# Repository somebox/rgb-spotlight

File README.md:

# RGB Spotlight

Status (2026-11-03): v2 schematics and both boards done (DRC clean), with a failure review whose changes are planned but not yet applied. Start with [HANDOVER.md](HANDOVER.md).

Chainable, addressable 3 x 3 W RGB spotlight for 12 V installations: an aluminium LED board and an FR4 driver board in an aluminium cylinder.

- **v1** (EasyEDA, one FR4 board) was built but never lit: the PT4115 stages were wired as the wrong kind of buck, and the 74HC04 was unpowered.
- **v2** is a KiCad restart with two boards.

| Document | What's in it |
| --- | --- |
| [HANDOVER.md](HANDOVER.md) | how we got here, decisions, the work remaining |
| [DESIGN.md](DESIGN.md) | requirements, the v1 post-mortem, numbered decisions, circuit, thermal estimate, simulation (§2.7), open items |
| [LAYOUT.md](LAYOUT.md) | both PCBs: floor plans, rules, scripted copper and routing, outline presets, checks |
| [PRODUCTION.md](PRODUCTION.md) | order files, order checklist (polarity!), harness and bring-up, costs |
| [docs/reviews/](docs/reviews/) | pre-order failure review: findings, bench list, firmware duties |

## What it does

A high-power, addressable RGB pixel for spotlights and creative lighting. It speaks the WS2811 protocol, so it daisy-chains and works with FastLED, WLED and other WS2811-compatible software.

- **LED board** (aluminium, 1 layer, 50 mm):
  - three XINGLIGHT HD2525 3 W LEDs (R/G/B), spread on a 12 mm-radius ring;
  - each LED on its own heat-spreading copper island;
  - six wire pads around a centre hole for the harness.
- **Driver board** (FR4, 2 layers, 50 mm), mounted 4–6 cm behind the LED board:
  - WS2811 pixel controller;
  - three PT4115 constant-current bucks (455 mA each);
  - level shifter on DIN; inverter for the PWM polarity;
  - 78L05 logic rail; TVS on the 12 V input.

## Electrical specs

- **Supply:** 12 V (the PT4115 regulates down to about 6 V at the end of a chain)
- **Data:** WS2811 protocol, 800 kHz, single wire; 3.3 V or 5 V at DIN
- **LED current:** about 455 mA per channel (`I = 0.1 V / 0.22 Ω`); LEDs rated 1 A / 3 W
- **Full white:** 5.0 W, 0.42 A at 12 V per light (simulated, DESIGN.md §2.7); drivers about 80 % efficient
- **Chaining:** JST XH connectors (3 A) pass 12 V/GND through: up to 5 lights per fused 12 V feed, 2.2–2.6 A (DESIGN.md §2.4). Use a 36 W supply for 4 lights and 60 W for 5, and add a feed per group after that.
- **Heat:** about 2.7 W in the LED board, which needs a heatsink: the housing's heat plate. About 0.9 W in the driver, mostly in the three Schottky diodes. See DESIGN.md §2.6–2.7.
- **Dimming:** brightness follows the 8-bit level within 5 % above 20 % and within 20 % down to 5 %. The lowest few levels are unreliable (DESIGN.md §2.7).

## Connections

| Connector | Where | Pins |
| --- | --- | --- |
| J1 IN | driver, back (JST XH 3, vertical) | 1 `12V`, 2 `DATA`, 3 `GND` |
| J2 OUT | driver, back (JST XH 3, vertical) | 1 `12V`, 2 `DATA`, 3 `GND` |
| J3 LED | driver, front (JST PH 6, vertical) | 1 `R+`, 2 `R-`, 3 `G+`, 4 `G-`, 5 `B+`, 6 `B-` |
| TP1–TP6 | LED board, around the centre hole | same order as J3; solder the wires here |

J1 and J2 share one pin order, so chain with pin-1-to-pin-1 cables. v1 had J2 mirrored.

1. Connect the controller's data to J1 pin 2 of the first light, and +12 V / GND to pins 1 / 3. Keep controller and power grounds common.
2. Chain J2 of one light to J1 of the next.
3. Twist each colour's LED pair in the harness.

## Project layout

- `boards/led/`, `boards/driver/`: KiCad 10 projects. Schematics come from `scripts/sch_led.py` / `scripts/sch_driver.py`; boards from `scripts/make_led_pcb.sh` / `scripts/make_driver_pcb.sh`.
- `lib/`: project symbols, footprints and 3D models (`scripts/make_lib.py`).
- `scripts/`: generators and checks (`netcheck.py`, `ratsnest.py`, `make_previews.sh`, `make_fab.sh`); `pcbkit.toml` sets up pcb-kit's release and production record. The shared parts (schematic builder, silkscreen placer, DRC/ERC/board checks, previews, JLC fab files, ngspice runner) come from [pcb-kit](https://github.com/somebox/pcb-kit): `uv tool install -e ~/src/pcb-kit && pcbkit link`.
- `sim/`: ngspice simulation of one LED channel (`sim/channel.py`); tables and plots in `sim/results/`.
- `docs/previews/<board>/`: schematic PDF, board PNGs, 3D renders. `docs/previews/outline-presets.png` compares the board outline options.
- **Board outline:** everything sits in a 50 mm core. The edge is a preset, `disc50` (current), `disc55`, `disc60` or `tabs3` (screw tabs). Change it with `scripts/set_outline.py`; see LAYOUT.md.
- `archive/v1-easyeda/`: the v1 EasyEDA exports, a KiCad import of the v1 board, its as-built netlist and the bodge guide.

```bash
python3 scripts/sch_driver.py && python3 scripts/sch_led.py
pcbkit erc boards/driver/driver.kicad_sch && python3 scripts/netcheck.py
scripts/make_led_pcb.sh && scripts/make_driver_pcb.sh --force --route
pcbkit drc boards/driver/driver.kicad_pcb --save && pcbkit check boards/driver/driver.kicad_pcb
scripts/make_previews.sh all
pcbkit release --dry-run                                    # then pcbkit release: versioned order files in releases/ (PRODUCTION.md)
python3 sim/channel.py                                      # LED channel simulation
```

## BOM

- Driver: 19 lines, about $2.18 at qty 1. LED board: 3 lines, about $0.77 (bomi, 2026-10-05).
- Each board has its own bomi project:

```bash
bomi --project boards/driver list --check
bomi --project boards/driver list --format markdown > docs/BOM_driver.md
bomi --project boards/led list --format markdown > docs/BOM_led.md
```

See [docs/BOM_driver.md](docs/BOM_driver.md), [docs/BOM_led.md](docs/BOM_led.md) and DESIGN.md §3. The v1 rationale doc is in `archive/v1-easyeda/rgb-spotlight-bom-v1.md`; its PT4115 connection tables are wrong.

## v1 (for reference)

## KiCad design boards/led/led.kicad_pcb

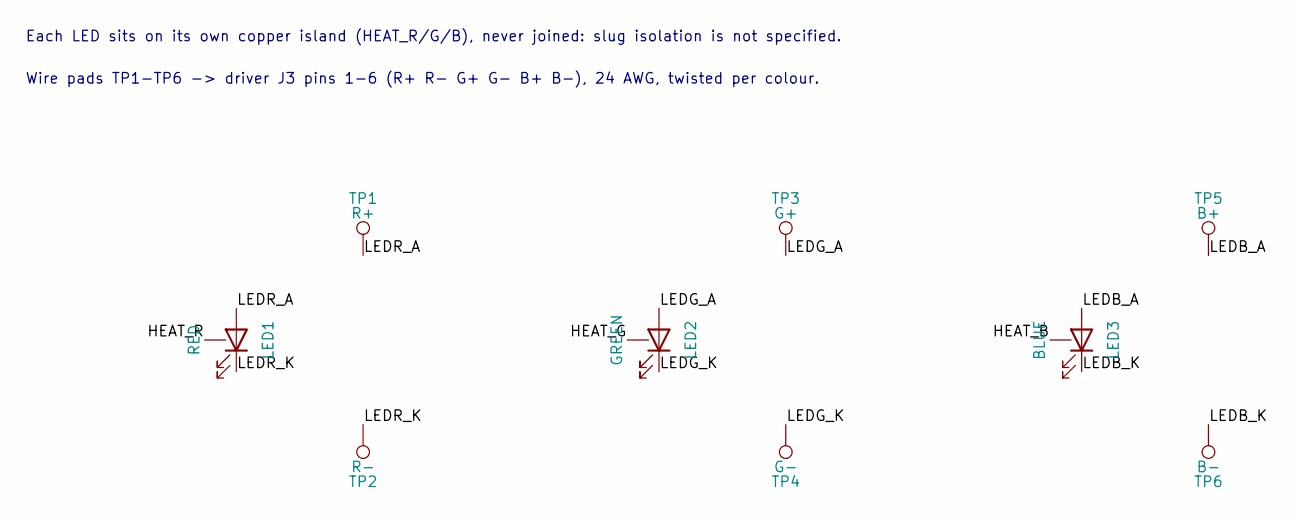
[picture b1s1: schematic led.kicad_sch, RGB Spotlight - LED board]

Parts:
LED1: RED; LED_XINGLIGHT_HD2525; MPN XL-HD2525SURC-A4; LCSC C49237857
LED2: GREEN; LED_XINGLIGHT_HD2525; MPN XL-HD2525UGC-A4; LCSC C49237859
LED3: BLUE; LED_XINGLIGHT_HD2525; MPN XL-HD2525UBC-A4; LCSC C49237860
TP1: R+; WirePad_2.2x3.5mm
TP2: R-; WirePad_2.2x3.5mm
TP3: G+; WirePad_2.2x3.5mm
TP4: G-; WirePad_2.2x3.5mm
TP5: B+; WirePad_2.2x3.5mm
TP6: B-; WirePad_2.2x3.5mm

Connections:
/HEAT_B: LED3.3 (PAD)
/HEAT_G: LED2.3 (PAD)
/HEAT_R: LED1.3 (PAD)
/LEDB_A: LED3.2 (A), TP5.1
/LEDB_K: LED3.1 (K), TP6.1
/LEDG_A: LED2.2 (A), TP3.1
/LEDG_K: LED2.1 (K), TP4.1
/LEDR_A: LED1.2 (A), TP1.1
/LEDR_K: LED1.1 (K), TP2.1

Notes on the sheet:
Each LED sits on its own copper island (HEAT_R/G/B), never joined: slug isolation is not specified.
Wire pads TP1-TP6 -> driver J3 pins 1-6 (R+ R- G+ G- B+ B-), 24 AWG, twisted per colour.

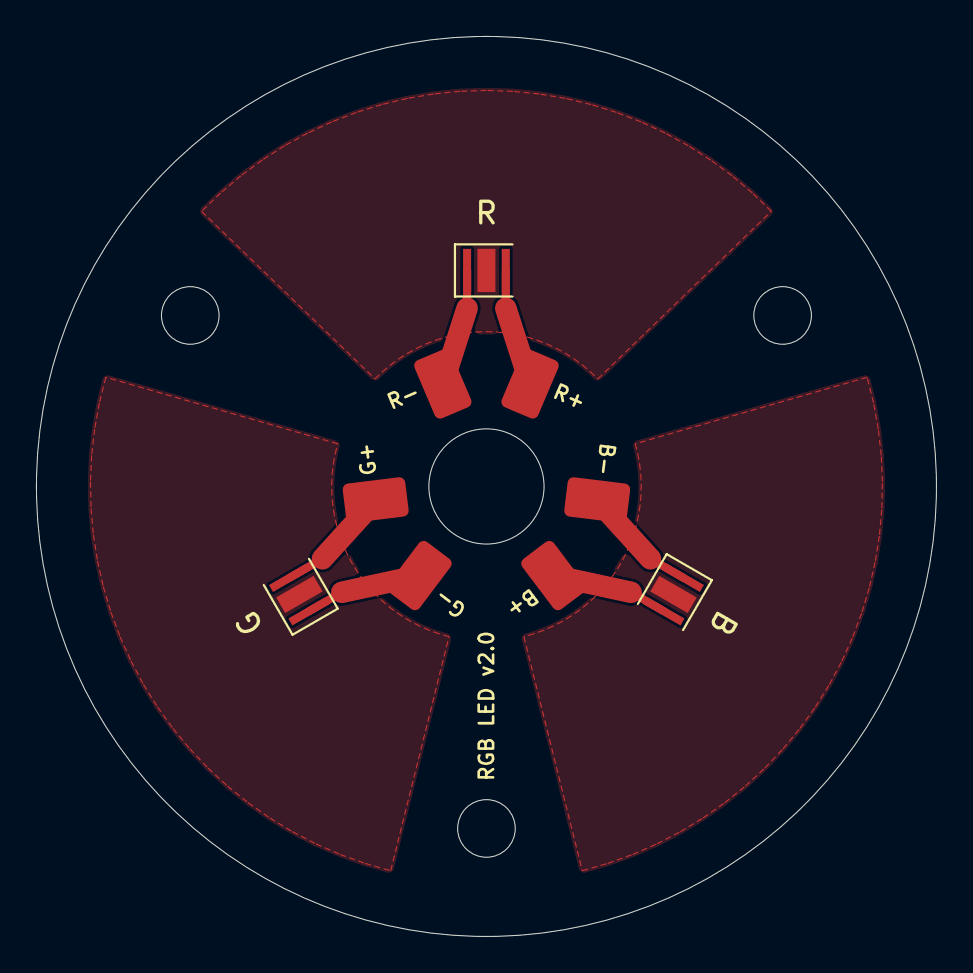
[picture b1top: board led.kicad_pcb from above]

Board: 2 copper layers, 50.0 x 50.0 mm, 12 parts (0 on the bottom side), 6 nets.

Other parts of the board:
H1, H2, H3: M3; MountingHole_3.2mm_M3

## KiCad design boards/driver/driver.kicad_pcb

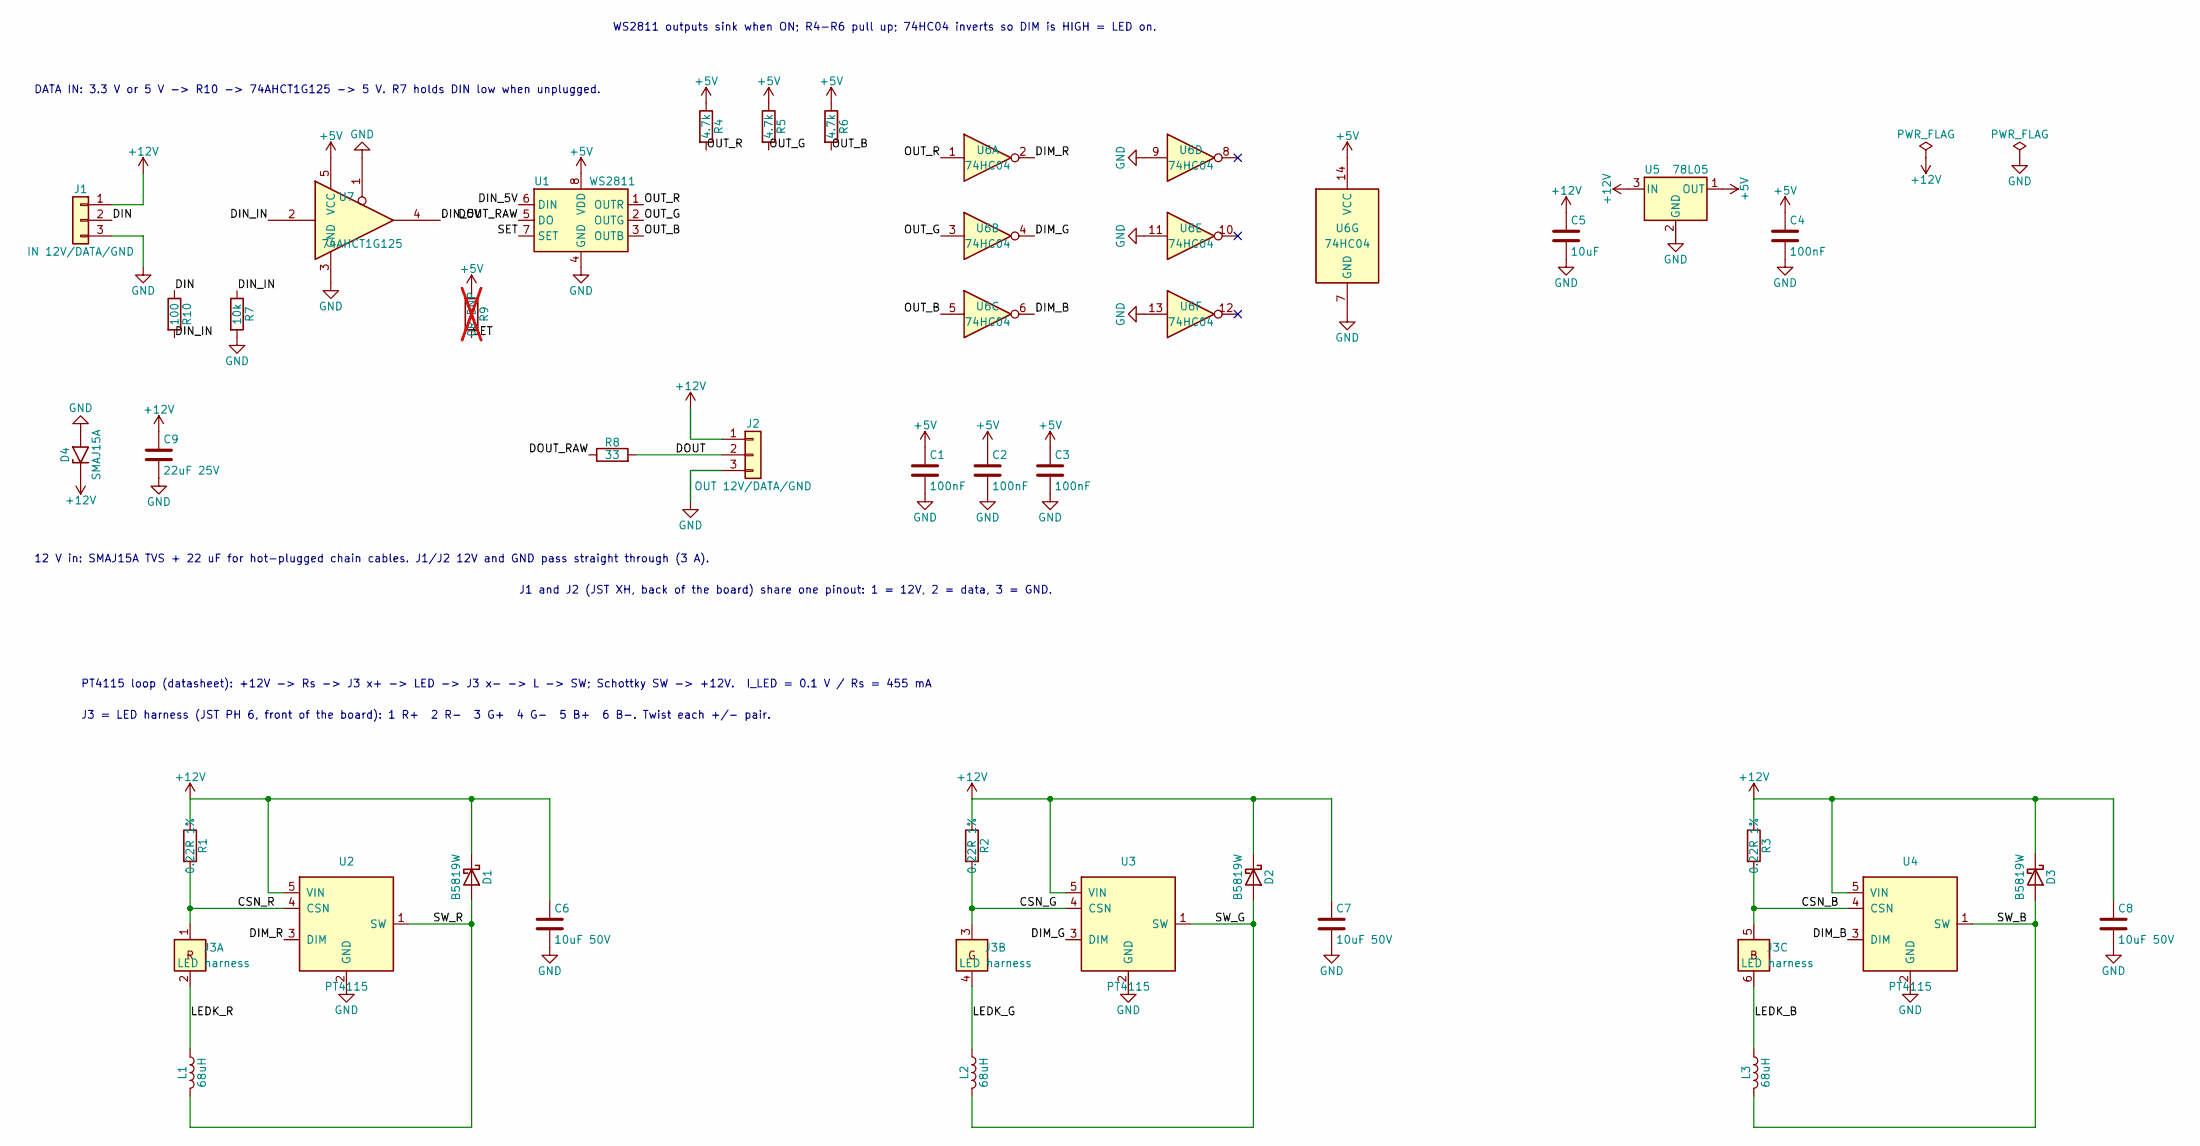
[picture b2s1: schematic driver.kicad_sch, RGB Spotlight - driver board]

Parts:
C1, C2, C3, C4: 100nF; C_0402_1005Metric; LCSC C1525
C5: 10uF; C_0805_2012Metric; LCSC C15850
C6, C7, C8: 10uF 50V; C_1206_3216Metric; MPN CL31A106KBHNNNE; LCSC C13585
C9: 22uF 25V; C_1206_3216Metric; MPN CL31A226KAHNNNE; LCSC C12891
D1, D2, D3: B5819W; D_SOD-123; LCSC C64885
D4: SMAJ15A; D_SMA; LCSC C19077535
J1: IN 12V/DATA/GND; JST_XH_B3B-XH-A_1x03_P2.50mm_Vertical; MPN B3B-XH-A(LF)(SN); LCSC C144394
J2: OUT 12V/DATA/GND; JST_XH_B3B-XH-A_1x03_P2.50mm_Vertical; MPN B3B-XH-A(LF)(SN); LCSC C144394
J3: LED harness; JST_PH_B6B-PH-K_1x06_P2.00mm_Vertical; MPN B6B-PH-K-S(LF)(SN); LCSC C131342
L1, L2, L3: 68uH; L_Changjiang_FNR6045S; MPN FNR6045S680MT; LCSC C168091
R1, R2, R3: 0.22R 1%; R_1206_3216Metric; MPN FRL1206FR220TS; LCSC C2907349
R4, R5, R6: 4.7k; R_0402_1005Metric; LCSC C25900
R7: 10k; R_0402_1005Metric; LCSC C25744
R8: 33; R_0402_1005Metric; LCSC C25105
R9: 0R DNP; R_0402_1005Metric; not fitted
R10: 100; R_0402_1005Metric; LCSC C25076
U1: WS2811; SOIC-8_3.9x4.9mm_P1.27mm; LCSC C114581
U2, U3, U4: PT4115; SOT-89-5; LCSC C347356
U5: 78L05; SOT-89-3; MPN 78L05G-AB3-R; LCSC C71136
U6: 74HC04; SOIC-14_3.9x8.7mm_P1.27mm; MPN 74HC04D,653; LCSC C5590
U7: 74AHCT1G125; SOT-353_SC-70-5; MPN SN74AHCT1G125DCKR; LCSC C350557

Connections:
+5V: C1.1, C2.1, C3.1, C4.1, R4.1, R5.1, R6.1, R9.1, U1.8 (VDD), U5.1 (OUT), U6.14 (VCC), U7.5 (VCC)
+12V: C5.1, C6.1, C7.1, C8.1, C9.1, D1.1 (K), D2.1 (K), D3.1 (K), D4.1 (A1), J1.1, J2.1, R1.1, R2.1, R3.1, U2.5 (VIN), U3.5 (VIN), U4.5 (VIN), U5.3 (IN)
/CSN_B: J3.5 (B+), R3.2, U4.4 (CSN)
/CSN_G: J3.3 (G+), R2.2, U3.4 (CSN)
/CSN_R: J3.1 (R+), R1.2, U2.4 (CSN)
/DIM_B: U4.3 (DIM), U6.6
/DIM_G: U3.3 (DIM), U6.4
/DIM_R: U2.3 (DIM), U6.2
/DIN: J1.2, R10.1
/DIN_5V: U1.6 (DIN), U7.4
/DIN_IN: R7.1, R10.2, U7.2
/DOUT: J2.2, R8.2
/DOUT_RAW: R8.1, U1.5 (DO)
/LEDK_B: J3.6 (B-), L3.1
/LEDK_G: J3.4 (G-), L2.1
/LEDK_R: J3.2 (R-), L1.1
/OUT_B: R6.2, U1.3 (OUTB), U6.5
/OUT_G: R5.2, U1.2 (OUTG), U6.3
/OUT_R: R4.2, U1.1 (OUTR), U6.1
/SET: R9.2, U1.7 (SET)
/SW_B: D3.2 (A), L3.2, U4.1 (SW)
/SW_G: D2.2 (A), L2.2, U3.1 (SW)
/SW_R: D1.2 (A), L1.2, U2.1 (SW)
GND: C1.2, C2.2, C3.2, C4.2, C5.2, C6.2, C7.2, C8.2, C9.2, D4.2 (A2), J1.3, J2.3, R7.2, U1.4 (GND), U2.2 (GND), U3.2 (GND), U4.2 (GND), U5.2 (GND), U6.7 (GND), U6.9, U6.11, U6.13, U7.1, U7.3 (GND)

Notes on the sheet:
DATA IN: 3.3 V or 5 V -> R10 -> 74AHCT1G125 -> 5 V. R7 holds DIN low when unplugged.
12 V in: SMAJ15A TVS + 22 uF for hot-plugged chain cables. J1/J2 12V and GND pass straight through (3 A).
WS2811 outputs sink when ON; R4-R6 pull up; 74HC04 inverts so DIM is HIGH = LED on.
J1 and J2 (JST XH, back of the board) share one pinout: 1 = 12V, 2 = data, 3 = GND.
PT4115 loop (datasheet): +12V -> Rs -> J3 x+ -> LED -> J3 x- -> L -> SW; Schottky SW -> +12V. I_LED = 0.1 V / Rs = 455 mA
J3 = LED harness (JST PH 6, front of the board): 1 R+ 2 R- 3 G+ 4 G- 5 B+ 6 B-. Twist each +/- pair.

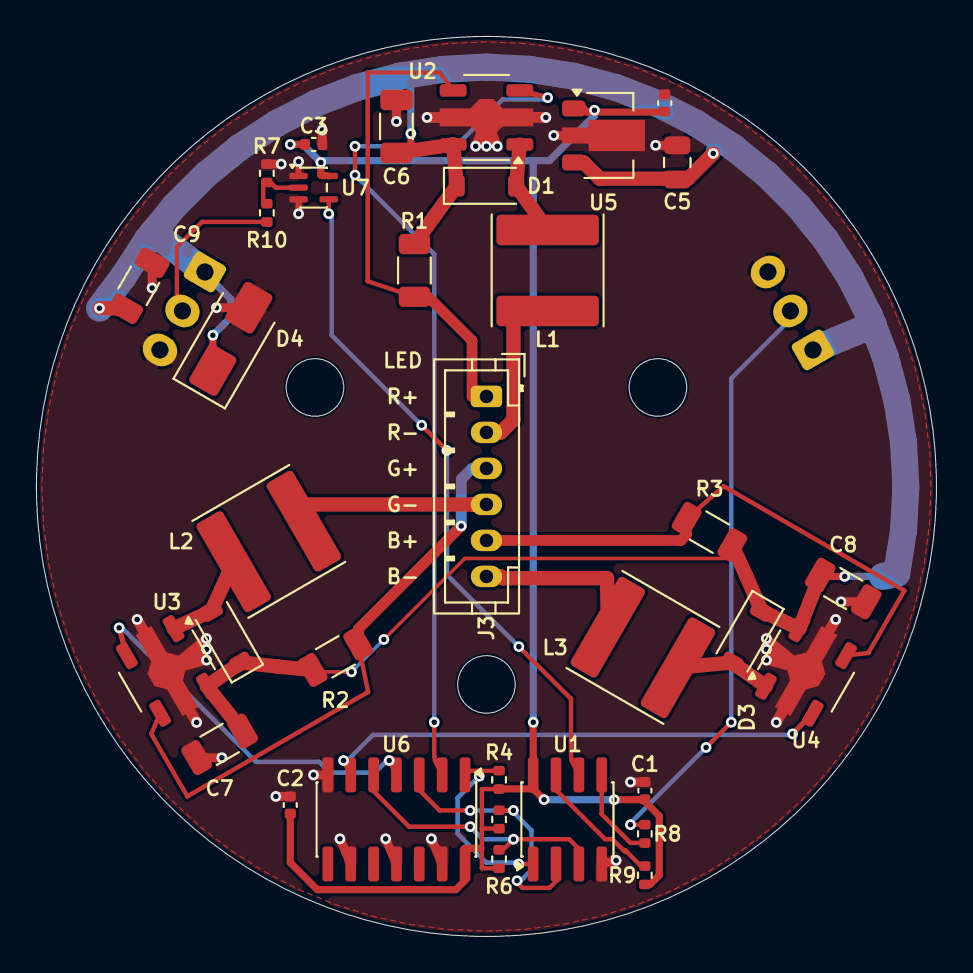
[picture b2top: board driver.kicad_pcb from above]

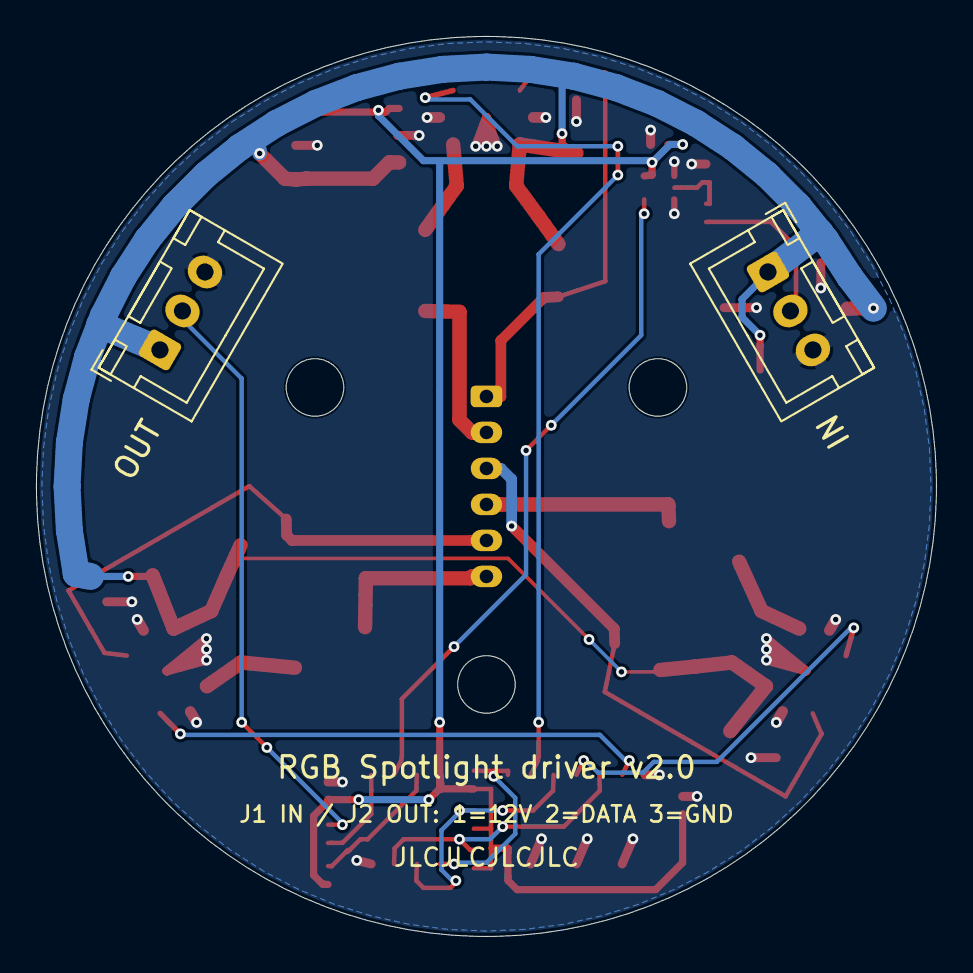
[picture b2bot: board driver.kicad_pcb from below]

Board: 2 copper layers, 50.0 x 50.0 mm, 39 parts (2 on the bottom side), 24 nets.

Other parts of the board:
H1, H2, H3: M3; MountingHole_3.2mm_M3

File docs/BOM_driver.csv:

Ref,LCSC,Qty,Part,Manufacturer,Package,Description,Price,Stock,Type,Notes,Datasheet,JLCPCB URL
C1-C4,C1525,4,CL05B104KO5NNNC,Samsung Electro-Mechanics,0402,100nF 16V X7R ±10% 0402 Multilayer Ceramic Capacitors MLCC - SMD/SMT ROHS,0.0045,22162126,base,"100nF X7R bypass: C1 WS2811, C2 74HC04, C3 74AHCT1G125, C4 78L05 out",https://www.lcsc.com/datasheet/lcsc_datasheet_2304140030_Sam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,https://jlcpcb.com/partdetail/1877-CL05B104KO5NNNC/C1525
C5,C15850,1,CL21A106KAYNNNE,Samsung Electro-Mechanics,0805,10uF 25V X5R ±10% 0805 Multilayer Ceramic Capacitors MLCC - SMD/SMT ROHS,0.0651,4918817,base,"10uF 25V 0805, 78L05 input",https://www.lcsc.com/datasheet/lcsc_datasheet_2304140030_Sam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,https://jlcpcb.com/partdetail/16532-CL21A106KAYNNNE/C15850
C6-C8,C13585,3,CL31A106KBHNNNE,Samsung Electro-Mechanics,1206,10uF 50V X5R ±10% 1206 Multilayer Ceramic Capacitors MLCC - SMD/SMT ROHS,0.2655,2382882,base,"10uF 50V X5R 1206, PT4115 VIN bypass (>=4.7uF after DC bias at 12V)",https://www.lcsc.com/datasheet/lcsc_datasheet_2304140030_Sam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,https://jlcpcb.com/partdetail/14236-CL31A106KBHNNNE/C13585
C9,C12891,1,CL31A226KAHNNNE,Samsung Electro-Mechanics,1206,22uF 25V X5R ±10% 1206 Multilayer Ceramic Capacitors MLCC - SMD/SMT ROHS,0.0494,1082676,base,"22uF 25V X5R 1206, 12V input bulk",https://www.lcsc.com/datasheet/lcsc_datasheet_2304140030_Sam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,https://jlcpcb.com/partdetail/13537-CL31A226KAHNNNE/C12891
D1-D3,C64885,3,B5819W,MDD(Microdiode Semiconductor),SOD-123,-55℃~+125℃ 1.5A 1mA@40V 25A 40V 600mV@1A Standalone SOD-123 Schottky Diodes ROHS,0.0194,933876,expand,B5819W 40V/1A Schottky freewheeling diode,https://www.lcsc.com/datasheet/lcsc_datasheet_2407291648_MDD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,https://jlcpcb.com/partdetail/MDD_Microdiode_Semiconductor-B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
D4,C19077535,1,SMAJ15A,hongjiacheng,DO-214AC(SMA),-55℃~+150℃ 1 15V 16.4A@10/1000us 18.5V 1uA 24.4V 400W@10/1000us IEC 61000-4-2 TVS Unidirectional DO-214AC(SMA) ESD and Surge Protection (TVS/ESD) ROHS,0.0371,109695,expand,SMAJ15A TVS on +12V (hot-plugged chain cables),https://www.lcsc.com/datasheet/lcsc_datasheet_2411041728_hon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,https://jlcpcb.com/partdetail/hongjiacheng-SMAJ15A/C19077535
J1-J2,C144394,2,B3B-XH-A(LF)(SN),JST,"Plugin,P=2.5mm","-25℃~+85℃ 1 1x3P 2.5mm 250V 3 3A 3P 5.75mm 7mm 9.9mm Brass K Pin PA66 Through Hole Tin UL94V-0 White XH 插件,P=2.5mm Wire To Board Connector ROHS",0.0542,175004,expand,"JST XH 3P vertical THT (3 A), IN/OUT on the back: 1=12V 2=DATA 3=GND",https://www.lcsc.com/datasheet/lcsc_datasheet_2304140030_JST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,https://jlcpcb.com/partdetail/JST-B3B_XH_A_LF_SN/C144394
J3,C131342,1,B6B-PH-K-S(LF)(SN),JST,"Plugin,P=2mm","-25℃~+85℃ 1 100V 13.9mm 1x6P 2A 2mm 4.5mm 6 6P 6mm Brass K Pin PA66 PH Through Hole Tin UL94V-0 White 插件,P=2mm Wire To Board Connector ROHS",0.0722,74983,expand,"JST PH 6P vertical THT, LED harness: R+ R- G+ G- B+ B-",https://www.lcsc.com/datasheet/lcsc_datasheet_1811151524_JST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,https://jlcpcb.com/partdetail/JST-B6B_PH_K_S_LF_SN/C131342
L1-L3,C168091,3,FNR6045S680MT,cjiang (Changjiang Microelectronics Tech),"SMD,6x6mm","1.1A 1.3A 376mΩ 68uH Magnetic Shielded Inductor ±20% SMD,6x6mm Power Inductors ROHS",0.0695,34298,expand,"68uH FNR6045S680MT, Isat 1.1A; PT4115 table 47-68uH for 0.4-0.8A",https://www.lcsc.com/datasheet/lcsc_datasheet_2304140030_cji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,https://jlcpcb.com/partdetail/179474-FNR6045S680MT/C168091
R1-R3,C2907349,3,FRL1206FR220TS,FOJAN,1206,-55℃~+155℃ 220mΩ 250mW 500V Thick Film Resistor ±1% ±300ppm/℃ 1206 Chip Resistor - Surface Mount ROHS,0.0071,43689,expand,"0.22R 1% 1206 300ppm, current sense: 0.1V/0.22R = 455mA",https://wmsc.lcsc.com/wmsc/upload/file/pdf/v2/lcsc/230824194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,https://jlcpcb.com/partdetail/FOJAN-FRL1206FR220TS/C2907349
R4-R6,C25900,3,0402WGF4701TCE,UNI-ROYAL(Uniroyal Elec),0402,-55℃~+155℃ 4.7kΩ 50V 62.5mW Thick Film Resistor ±1% ±100ppm/℃ 0402 Chip Resistor - Surface Mount ROHS,0.0027,15438980,base,4.7k pull-up for WS2811 open-drain outputs,https://www.lcsc.com/datasheet/lcsc_datasheet_2206010045_UNI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,https://jlcpcb.com/partdetail/26643-0402WGF4701TCE/C25900
R7,C25744,1,0402WGF1002TCE,UNI-ROYAL(Uniroyal Elec),0402,-55℃~+155℃ 10kΩ 50V 62.5mW Thick Film Resistor ±1% ±100ppm/℃ 0402 Chip Resistor - Surface Mount ROHS,0.0034,21677422,base,10k DIN pull-down (defined low when unplugged),https://www.lcsc.com/datasheet/lcsc_datasheet_2411221126_UNI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,https://jlcpcb.com/partdetail/26487-0402WGF1002TCE/C25744
R8,C25105,1,0402WGF330JTCE,UNI-ROYAL(Uniroyal Elec),0402,-55℃~+155℃ 33Ω 50V 62.5mW Thick Film Resistor ±1% ±100ppm/℃ 0402 Chip Resistor - Surface Mount ROHS,0.0012,1815221,base,33R series on DOUT (cable source termination),https://www.lcsc.com/datasheet/lcsc_datasheet_2205311900_UNI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,https://jlcpcb.com/partdetail/25848-0402WGF330JTCE/C25105
R10,C25076,1,0402WGF1000TCE,UNI-ROYAL(Uniroyal Elec),0402,-55℃~+155℃ 100Ω 50V 62.5mW Thick Film Resistor ±1% ±100ppm/℃ 0402 Chip Resistor - Surface Mount ROHS,0.0008,2868420,base,100R series on DIN,https://www.lcsc.com/datasheet/lcsc_datasheet_2205311900_UNI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,https://jlcpcb.com/partdetail/25819-0402WGF1000TCE/C25076
U1,C114581,1,WS2811,Worldsemi,SOP-8,-25℃~+85℃ 16.5mA 20V 3 5V~24V 800kHz Over Voltage Protection、Short-Circuit  Protection PWM SOP-8 LED Drivers ROHS,0.0413,111712,expand,"WS2811 pixel controller, SET pin floated for 800kHz",https://www.lcsc.com/datasheet/lcsc_datasheet_1810081420_Wor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,https://jlcpcb.com/partdetail/Worldsemi-WS2811/C114581
U2-U4,C347356,3,PT4115,"UMW(Youtai Semiconductor Co., Ltd.)",SOT-89-5,-25℃~+85℃ 1.2A 1MHz 5% 6V~30V Analog、PWM Buck Built-in DC-DC Over-Temperature Protection (OTP) SOT-89-5 LED Drivers ROHS,0.1104,100444,expand,"PT4115 buck LED driver, one per RGB channel",https://www.lcsc.com/datasheet/lcsc_datasheet_1912111437_UMW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,https://jlcpcb.com/partdetail/324016-PT4115/C347356
U5,C71136,1,78L05G-AB3-R,UTC(Unisonic Tech),SOT-89-3,"-40℃~+85℃ 1 1.7V@(40mA) 100mA 2mA 30V 40uV 5V 80dB@(120Hz) Fixed Over Current Protection、Short Circuit Protection、Thermal Shutdown Positive SOT-89-3 Voltage Regulators - Linear, Low Drop Out (LDO) Regulators ROHS",0.0893,226961,base,"78L05 5V regulator, basic part",https://www.lcsc.com/datasheet/lcsc_datasheet_2304140030_UTC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,https://jlcpcb.com/partdetail/UTC_Unisonic_Tech-78L05G_AB3R/C71136
U6,C5590,1,"74HC04D,653",Nexperia,SOIC-14,"-40℃~+125℃ 1 1.5V~4.2V 1.9V、3.7V、5.2V 100mV、400mV、400mV 14ns@6V,50pF 2V~6V 2uA 5.2mA 5.2mA 500mV~1.8V 6 74HC SOIC-14 Inverters ROHS",0.1290,39344,expand,"74HC04 hex inverter, WS2811 open-drain inversion",https://www.lcsc.com/datasheet/lcsc_datasheet_2407241044_Nex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,https://jlcpcb.com/partdetail/Nexperia-74HC04D653/C5590
U7,C350557,1,SN74AHCT1G125DCKR,Texas Instruments,SC-70-5,"-40℃~+125℃ 1 1 10uA 4.5V~5.5V 5.5ns@5V,15pF 74AHCT 8mA 8mA Tri-State Unidirectional SC-70-5 Buffers, Drivers, Receivers, Transceivers ROHS",0.1418,17039,expand,SN74AHCT1G125 3.3V-to-5V level shifter on DIN,https://www.lcsc.com/datasheet/lcsc_datasheet_1912111437_Tex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,https://jlcpcb.com/partdetail/TexasInstruments-SN74AHCT1G125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

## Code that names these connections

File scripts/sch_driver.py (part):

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comps = [
    # ---- data in: J1 -> R10 100R -> (R7 10k pull-down) -> 74AHCT1G125 (3.3 V -> 5 V) -> WS2811 DIN
    dict(ref="J1", lib="Connector_Generic:Conn_01x03", val="IN 12V/DATA/GND", fp=XH3, x=30.48, y=60.96, mirror="y",
         lcsc="C144394", fields={"MPN": "B3B-XH-A(LF)(SN)"}, pins={"1": None, "2": "DIN", "3": None}),
    r("R10", "100", "C25076", 45.72, 76.2, "DIN", "DIN_IN"),
    r("R7", "10k", "C25744", 55.88, 76.2, "DIN_IN", "GND"),
    dict(ref="U7", lib="74xGxx:74AHCT1G125", val="74AHCT1G125", fp="Package_TO_SOT_SMD:SOT-353_SC-70-5",
         x=76.2, y=60.96, lcsc="C350557", fields={"MPN": "SN74AHCT1G125DCKR"},
         pins={"1": "GND", "2": "DIN_IN", "3": "GND", "4": "DIN_5V", "5": "+5V"}),
    # ---- 12 V input protection (hot-plugged chain cables): TVS + bulk
    dict(ref="D4", lib="Diode:SMAJ15A", val="SMAJ15A", fp="Diode_SMD:D_SMA", x=30.48, y=99.06, rot=90, lcsc="C19077535",
         pins={"1": "+12V", "2": "GND"}),
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    # ---- WS2811: open-drain outputs, pulled up to 5 V, inverted by the 74HC04 (DESIGN.md §2.3)
    dict(ref="U1", lib="Driver_LED:WS2811", val="WS2811", fp="Package_SO:SOIC-8_3.9x4.9mm_P1.27mm",
         x=111.76, y=60.96, lcsc="C114581",
         pins={"1": "OUT_R", "2": "OUT_G", "3": "OUT_B", "4": "GND", "5": "DOUT_RAW", "6": "DIN_5V", "7": "SET", "8": "+5V"}),
    r("R9", "0R DNP", "", 93.98, 76.2, "+5V", "SET"),   # SET strap, unfitted: Worldsemi V2.2 says NC, older/clone WS2811s use it for 400/800k
    r("R4", "4.7k", "C25900", 132.08, 45.72, "+5V", "OUT_R"),
    r("R5", "4.7k", "C25900", 142.24, 45.72, "+5V", "OUT_G"),
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         lcsc="C144394", fields={"MPN": "B3B-XH-A(LF)(SN)"}, pins={"1": None, "2": None, "3": None}),
    # ---- 74HC04: gates 1-3 invert OUT_x -> DIM_x; gates 4-6 inputs to GND, outputs open; unit 7 = power
    dict(ref="U6", unit=1, lib="74xx:74HC04", val="74HC04", fp="Package_SO:SOIC-14_3.9x8.7mm_P1.27mm",
         x=177.8, y=50.8, lcsc="C5590", fields={"MPN": "74HC04D,653"}, pins={"1": "OUT_R", "2": "DIM_R"}),
    dict(ref="U6", unit=2, lib="74xx:74HC04", x=177.8, y=63.5, pins={"3": "OUT_G", "4": "DIM_G"}),
    dict(ref="U6", unit=3, lib="74xx:74HC04", x=177.8, y=76.2, pins={"5": "OUT_B", "6": "DIM_B"}),
    dict(ref="U6", unit=4, lib="74xx:74HC04", x=210.82, y=50.8, pins={"9": "GND", "8": "NC"}),
    dict(ref="U6", unit=5, lib="74xx:74HC04", x=210.82, y=63.5, pins={"11": "GND", "10": "NC"}),
    dict(ref="U6", unit=6, lib="74xx:74HC04", x=210.82, y=76.2, pins={"13": "GND", "12": "NC"}),
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
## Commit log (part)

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2026-03-28 update bom to use https://github.com/somebox/bomi for part tracking
2026-04-19 Update README.md to reflect changes in RGB spotlight specifications, including size, electrical specs, and connection details. Improved clarity and organization of content.
